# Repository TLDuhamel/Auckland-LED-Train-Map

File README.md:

# Auckland Live LED Train Map

**You can now support my work by buying this through my store:** [**https://keastudios.co.nz/store/akl-ltm/**](https://keastudios.co.nz/store/akl-ltm/)

A physical, real-time LED map of the Auckland train network, powered by an ESP32-C3 microcontroller. Train movements are displayed using addressable RGB LEDs, with live data fetched over Wi-Fi.

---

## Table of Contents

- [Auckland Live LED Train Map](#auckland-live-led-train-map)
  - [Table of Contents](#table-of-contents)
  - [Features](#features)
  - [Hardware](#hardware)
  - [PCB Design](#pcb-design)
  - [Software / Firmware](#software--firmware)
  - [Getting Started](#getting-started)
  - [Web Installer](#web-installer)
  - [Links](#links)
  - [Contributing](#contributing)
  - [License](#license)

---

## Features

- **Real-time Train Tracking:** Displays the approximate locations of trains on the Auckland network.
- **Addressable LEDs:** ~150 WS2812B-compatible RGB LEDs (1.6x1.5mm) for a vibrant display.
- **Wi-Fi Connectivity:** ESP32-C3's built-in Wi-Fi fetches live train data.
- **Custom PCB:** Designed for JLCPCB manufacturing limits.
- **Open Source:** Hardware and firmware are open source.

---

## Hardware

- **Microcontroller:** ESP32-C3 (RISC-V, 160 MHz, 4 MB Flash, QFN32)
- **LEDs:** ~150 x XL-1615RGBC-WS2812B (1.6mm x 1.5mm)
- **PCB:** 249mm x 66mm, JLCPCB-friendly
- **Antenna:** On-board PCB antenna ([TI CC2430DB design](https://www.ti.com/lit/ug/swru125/swru125.pdf))

---

## PCB Design

- Designed in **KiCad V9.0** using [JLCPCB KiCad Library](https://github.com/CDFER/jlcpcb-kicad-library)
- **View Online:** [Interactive PCB Layout (Kicanvas)](https://kicanvas.org/?github=https%3A%2F%2Fgithub.com%2FCDFER%2FAuckland-LED-Train-Map%2Ftree%2Fmain%2FPCB)
- **Source Files:** `/PCB` directory

---

## Software / Firmware

The ESP32-C3 firmware is responsible for:

1. Connecting to Wi-Fi
2. Fetching live train data from the [GTFS Realtime Cache API](https://github.com/CDFER/GTFS-Realtime-Cache-Server)
3. Processing data to determine train locations
4. Controlling WS2812B LEDs to display train positions

---

## Getting Started

1. **Flash the Firmware:**
   - Use the [Web Installer](#web-installer) (recommended, no drivers needed)
   - Or flash manually using PlatformIO (`Firmware/` directory)
2. **Connect to Wi-Fi:**
   - On first boot, use the web interface to configure Wi-Fi credentials.
3. **Power the Board:**
   - Use a 5V USB-C power supply capable of at least 1A.
4. **Enjoy the Live Map!**

---

## Web Installer

Easily flash the latest firmware to your ESP32-C3 using your browser:

[Open the Auckland LED Train Map Web Installer](https://cdfer.github.io/Auckland-LED-Train-Map/led-rails.html)

- Works with Chrome, Edge, or any Web Serial-compatible browser
- Follow on-screen instructions to connect and flash your device

---

## Links

- [Web Installer](https://cdfer.github.io/Auckland-LED-Train-Map/led-rails.html)
- [Interactive PCB Viewer](https://kicanvas.org/?github=https%3A%2F%2Fgithub.com%2FCDFER%2FAuckland-LED-Train-Map%2Ftree%2Fmain%2FPCB)
- [GTFS Realtime Cache API](https://github.com/CDFER/GTFS-Realtime-Cache-Server)
- [JLCPCB KiCad Library](https://github.com/CDFER/jlcpcb-kicad-library)

---

## Contributing

Contributions are welcome! Open an issue or submit a pull request for improvements, bug fixes, or feature suggestions.

---

## License

This project is released under the GPL-3.0-or-later license.

© 2025 Chris Dirks

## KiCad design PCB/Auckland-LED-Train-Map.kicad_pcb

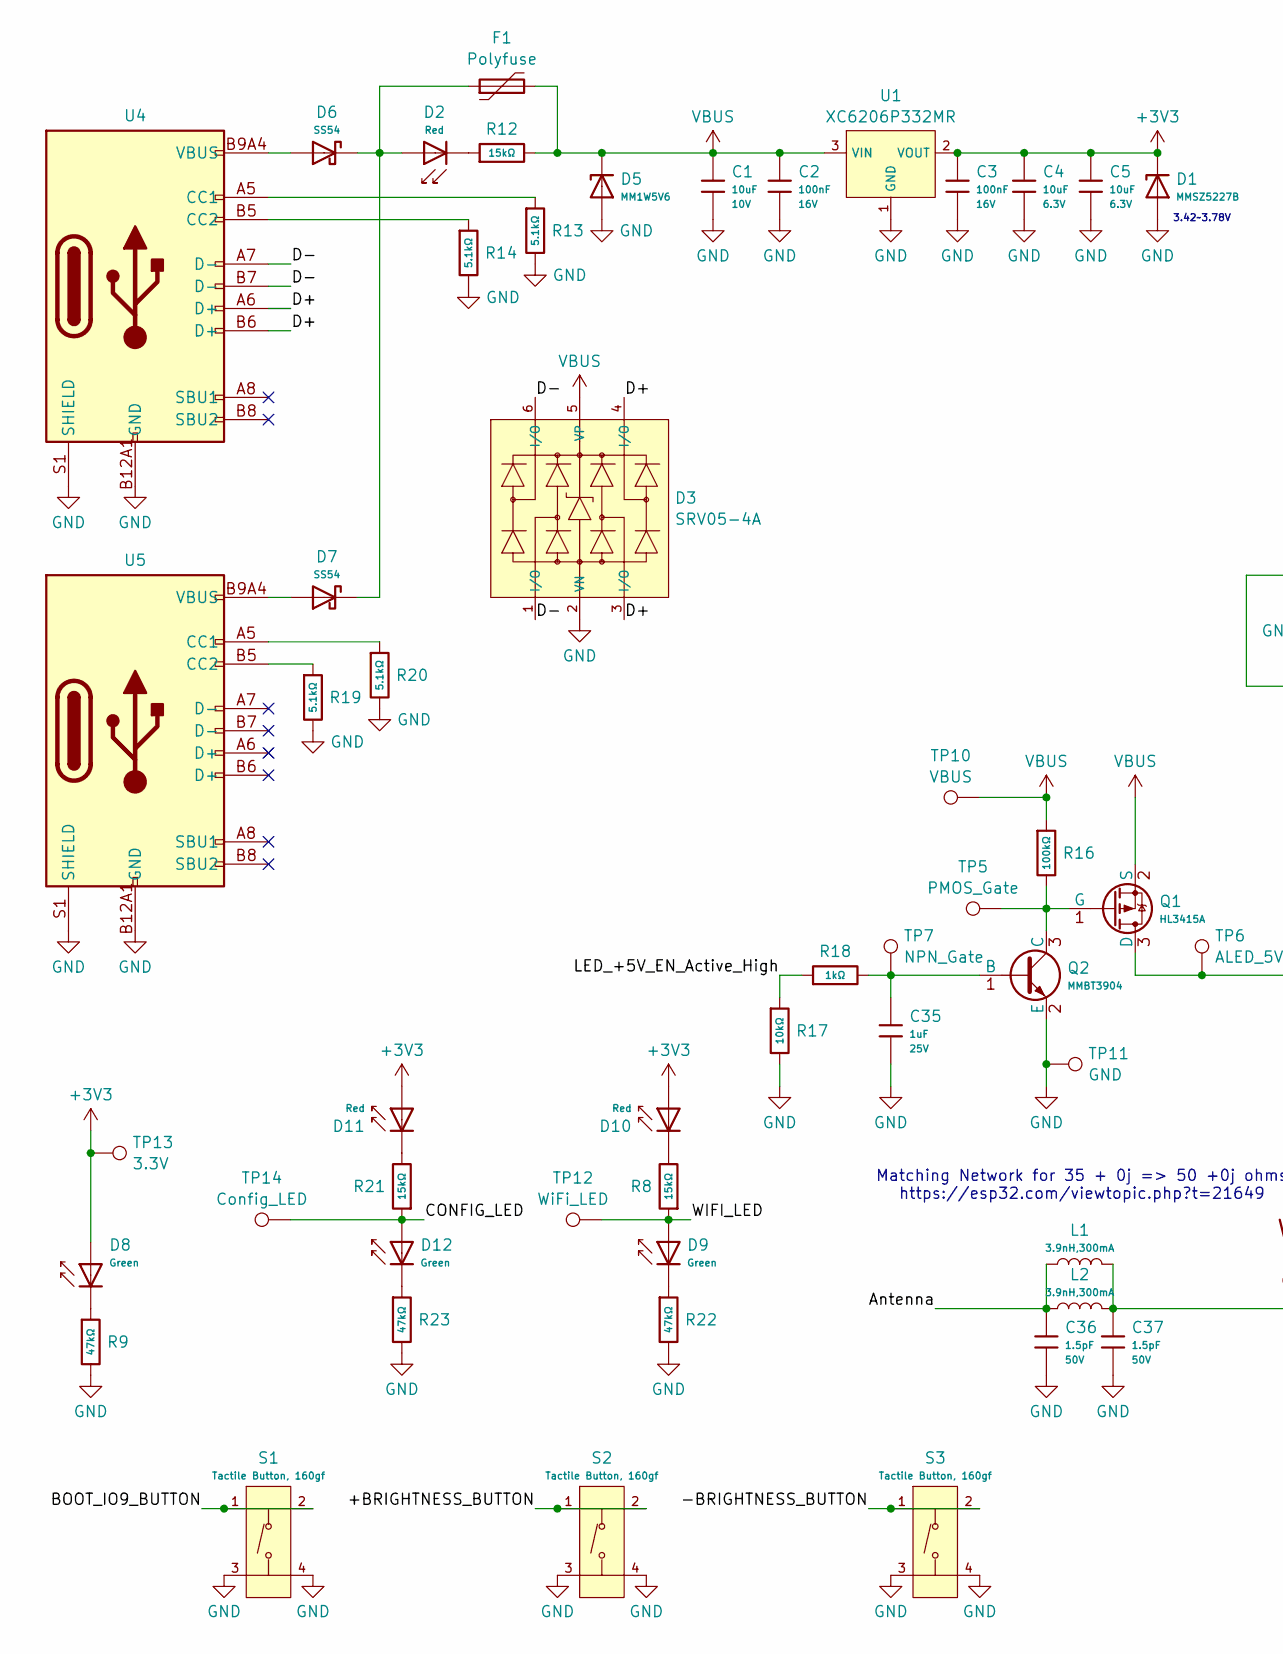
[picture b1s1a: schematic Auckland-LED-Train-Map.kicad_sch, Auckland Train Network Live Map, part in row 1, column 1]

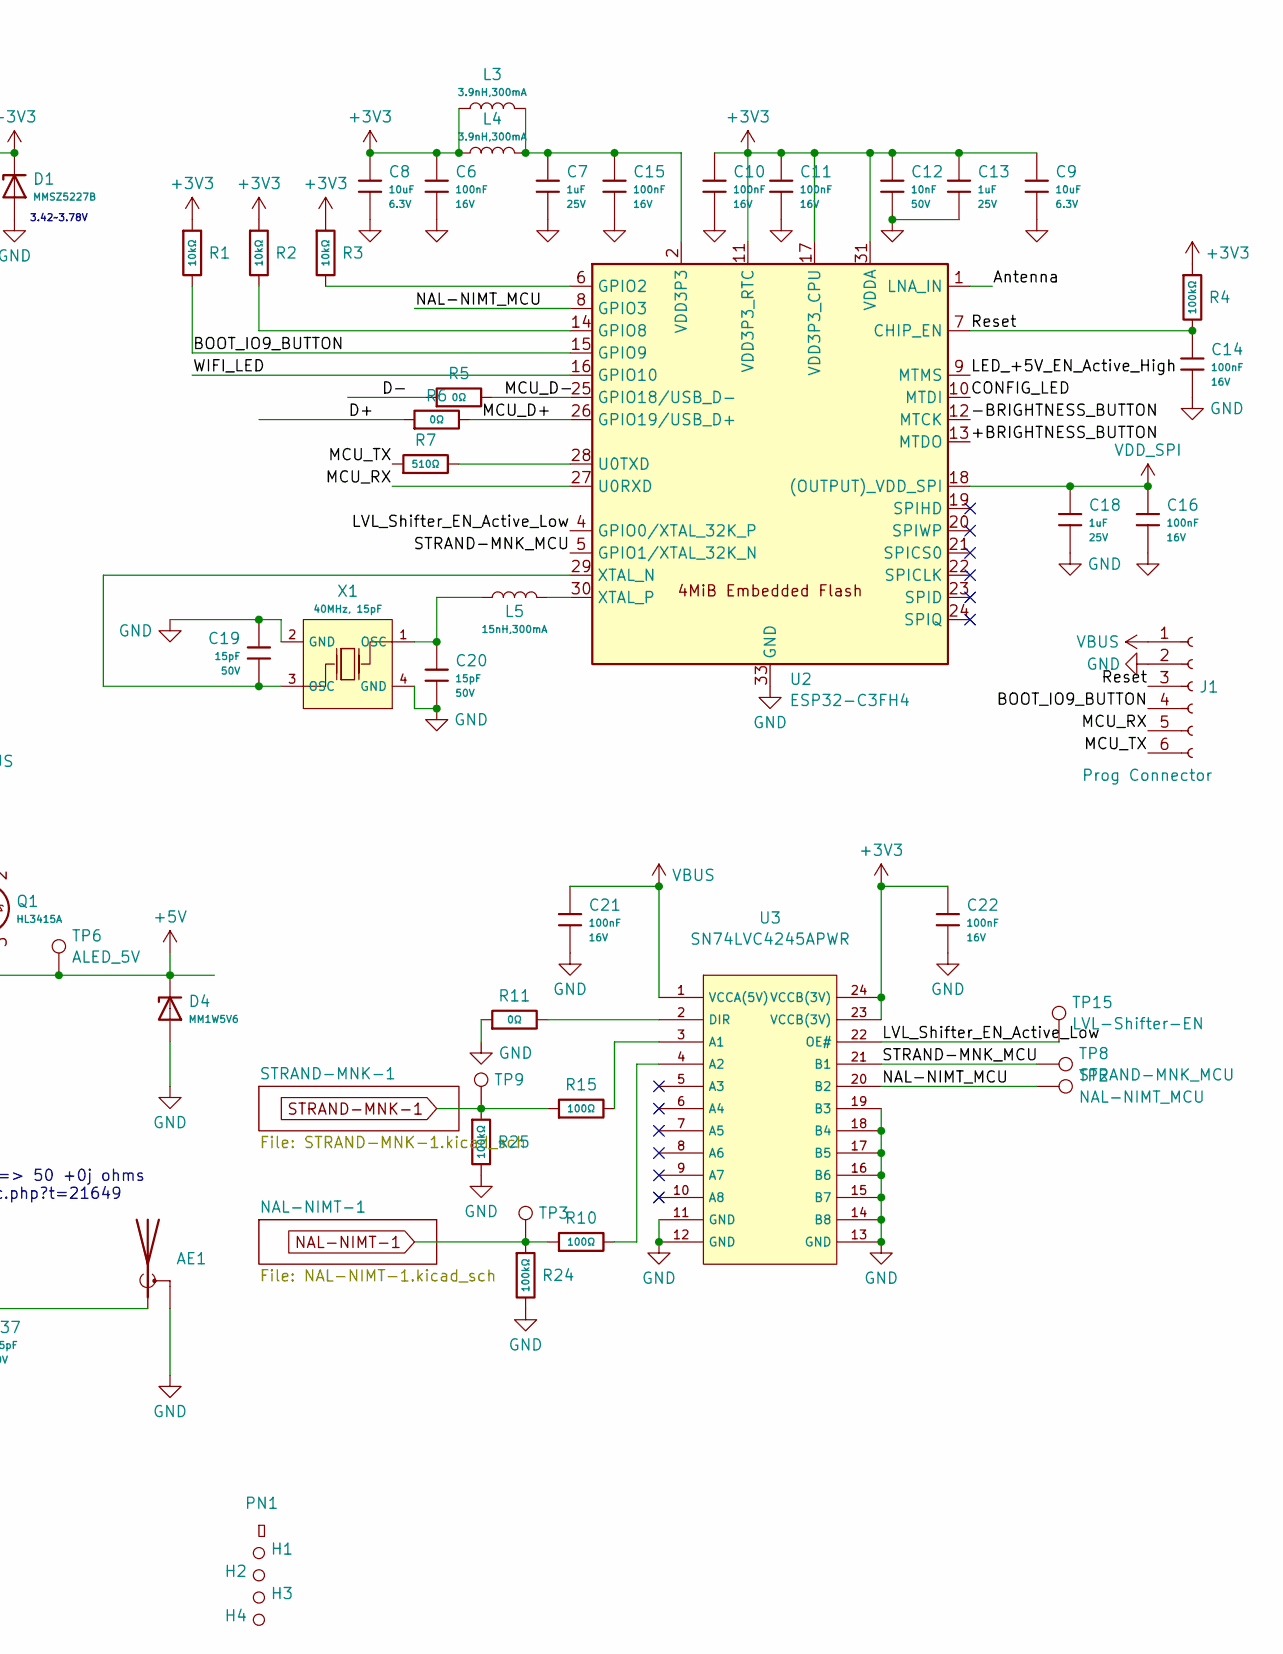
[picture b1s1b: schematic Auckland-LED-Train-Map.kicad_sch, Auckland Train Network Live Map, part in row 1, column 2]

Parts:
AE1: Antenna_Shield; Inverted_F_Antenna_2.4Ghz_1.0mmPCB_TI_CC2430DB.pretty
C1: 10uF; C_0603; Voltage Rated 10V; Tolerance ±10%; Part CL10A106KP8NNNC; LCSC C19702
C2, C3, C6, C10, C11, C14, C15, C16, C21, C22: 100nF; C_0402; Voltage Rated 16V; Tolerance ±10%; Part CL05B104KO5NNNC; LCSC C1525
C4, C5, C8, C9: 10uF; C_0402; Voltage Rated 6.3V; Tolerance ±20%; Part CL05A106MQ5NUNC; LCSC C15525
C7, C13, C18, C35: 1uF; C_0402; Voltage Rated 25V; Tolerance ±10%; Part CL05A105KA5NQNC; LCSC C52923
C12: 10nF; C_0402; Voltage Rated 50V; Tolerance ±10%; Part CL05B103KB5NNNC; LCSC C15195
C19, C20: 15pF; C_0402; Voltage Rated 50V; Tolerance ±5%; Part 0402CG150J500NT; LCSC C1548
C36, C37: 1.5pF; C_0402; Voltage Rated 50V; Part 0402CG1R5C500NT; LCSC C1552
D1: MMSZ5227B; D_SOD-123; Part MMSZ5227B; LCSC C22395553
D2, D10, D11: Red; D_0805; Forward Voltage (VF) 1.6V~2.6V; Part NCD0805R1; LCSC C84256
D3: SRV05-4A; SOT-23-6_L2.9-W1.6-P0.95-LS2.9-BL; Part SRV05-4A; LCSC C20615829
D4, D5: MM1W5V6; D_SOD-123; Part MM1W5V6; LCSC C22435086
D6, D7: SS54; D_SMA; Forward Voltage (Vf@If) 550mV@5A; Reverse Voltage (Vr) 40V; Part SS54; LCSC C22452
D8, D9, D12: Green; D_0805; Part KT-0805G; LCSC C2297
F1: Polyfuse; Fuse_0805_2012Metric_Pad1.15x1.40mm_HandSolder
H1, H2, H3, H4: Hole_Tooling_JLCPCB
J1: Prog Connector
L1, L2, L3, L4: 3.9nH,300mA; L_0402; Part SDCL1005C3N9STDF; LCSC C14033
L5: 15nH,300mA; L_0402; Tolerance ±5%; Part SDCL1005C15NJTDF; LCSC C27143
PN1: Part_Num_JLCPCB
Q1: HL3415A; Q_SOT-23; Part HL3415A; LCSC C28646270
Q2: MMBT3904; Q_SOT-23; Part MMBT3904; LCSC C7420353
R1, R2, R3, R17: 10kΩ; R_0402; Overload Voltage (Max) 50V; Tolerance ±1%; Part 0402WGF1002TCE; LCSC C25744
R4, R16, R24, R25: 100kΩ; R_0402; Overload Voltage (Max) 50V; Tolerance ±1%; Part 0402WGF1003TCE; LCSC C25741
R5, R6, R11: 0Ω; R_0402; Overload Voltage (Max) 50V; Tolerance ±1%; Part 0402WGF0000TCE; LCSC C17168
R7: 510Ω; R_0402; Overload Voltage (Max) 50V; Tolerance ±1%; Part 0402WGF5100TCE; LCSC C25123
R8, R12, R21: 15kΩ; R_0402; Overload Voltage (Max) 50V; Tolerance ±1%; Part 0402WGF1502TCE; LCSC C25756
R9, R22, R23: 47kΩ; R_0402; Overload Voltage (Max) 50V; Tolerance ±1%; Part 0402WGF4702TCE; LCSC C25792
R10, R15: 100Ω; R_0402; Overload Voltage (Max) 50V; Tolerance ±1%; Part 0402WGF1000TCE; LCSC C25076
R13, R14, R19, R20: 5.1kΩ; R_0402; Overload Voltage (Max) 50V; Tolerance ±1%; Part 0402WGF5101TCE; LCSC C25905
R18: 1kΩ; R_0402; Overload Voltage (Max) 50V; Tolerance ±1%; Part 0402WGF1001TCE; LCSC C11702
S1, S2, S3: Tactile Button, 160gf; SW-SMD_4P-L5.1-W5.1-P3.70-LS6.5-TL-2; Voltage Rating (Dc) 12V; Part TS-1187A-B-A-B; LCSC C318884
TP2: NAL-NIMT_MCU; TestPoint_Pad_D1.0mm
TP3: NAL-NIMT_LED; TestPoint_Pad_D1.0mm
TP5: PMOS_Gate; TestPoint_Pad_D1.0mm
TP6: ALED_5V; TestPoint_Pad_D1.0mm
TP7: NPN_Gate; TestPoint_Pad_D1.0mm
TP8: STRAND-MNK_MCU; TestPoint_Pad_D1.0mm
TP9: STRAND-MNK_LED; TestPoint_Pad_D1.0mm
TP10: VBUS; TestPoint_Pad_D1.0mm
TP11: GND; TestPoint_Pad_D1.0mm
TP12: WiFi_LED; TestPoint_Pad_D1.0mm
TP13: 3.3V; TestPoint_Pad_D1.0mm
TP14: Config_LED; TestPoint_Pad_D1.0mm
TP15: LVL-Shifter-EN; TestPoint_Pad_D1.0mm
U1: XC6206P332MR; SOT-23-3_L2.9-W1.6-P1.90-LS2.8-BR; Output Voltage 3.3V; Dropout Voltage 680mV@(100mA); Part XC6206P332MR-G; LCSC C5446
U2: ESP32-C3FH4; QFN-32-1EP_5x5mm_P0.5mm_EP3.7x3.7mm_ThermalVias; LCSC C2858491
U3: SN74LVC4245APWR; TSSOP-24_L7.8-W4.4-P0.65-LS6.4-BL; Part SN74LVC4245APWR; LCSC C7859
U4, U5: Connector, USB-TYPE-C-16P; TYPE-C-SMD_HX-TYPE-C-16PIN; LCSC C2927039
X1: 40MHz, 15pF; OSC-SMD_4P-L3.2-W2.5-BL_SIT8008BI; PartID X322540MPB4SI; LCSC C9010

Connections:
+3V3: C3.1, C4.1, C5.1, C6.1, C8.1, C9.1, C10.1, C11.1, C12.1, C13.1, C22.1, D1.1, D8.2, D10.2, D11.2, L3.1, L4.1, R1.1, R2.1, R3.1, R4.1, TP13.1, U1.2 (VOUT), U2.11 (VDD3P3_RTC), U2.17 (VDD3P3_CPU), U2.31 (VDDA), U2.32 (VDDA), U3.23 (VCCB(3V)), U3.24 (VCCB(3V))
+5V: D4.1, Q1.3 (D), TP6.1; also elsewhere on the board
/+BRIGHTNESS_BUTTON: S2.1 (A), S2.2 (B), U2.13 (MTDO)
/-BRIGHTNESS_BUTTON: S3.1 (A), S3.2 (B), U2.12 (MTCK)
/Antenna: C36.1, L1.1, L2.1, U2.1 (LNA_IN)
/BOOT_IO9_BUTTON: J1.4, R1.2, S1.1 (A), S1.2 (B), U2.15 (GPIO9)
/CONFIG_LED: D12.2, R21.1, TP14.1, U2.10 (MTDI)
/D+: D3.3 (I/O), D3.4 (I/O), R6.1, U4.A6 (D+), U4.B6 (D+)
/D-: D3.1 (I/O), D3.6 (I/O), R5.1, U4.A7 (D-), U4.B7 (D-)
/LED_+5V_EN_Active_High: R17.1, R18.1, U2.9 (MTMS)
/LVL_Shifter_EN_Active_Low: TP15.1, U2.4 (GPIO0/XTAL_32K_P), U3.22 (OE#)
/MCU_D+: R6.2, U2.26 (GPIO19/USB_D+)
/MCU_D-: R5.2, U2.25 (GPIO18/USB_D-)
/MCU_RX: J1.5, U2.27 (U0RXD)
/MCU_TX: J1.6, R7.1
/NAL-NIMT_MCU: TP2.1, U2.8 (GPIO3), U3.20 (B2)
/Reset: C14.1, J1.3, R4.2, U2.7 (CHIP_EN)
/STRAND-MNK_MCU: TP8.1, U2.5 (GPIO1/XTAL_32K_N), U3.21 (B1)
/WIFI_LED: D9.2, R8.1, TP12.1, U2.16 (GPIO10)
GND: AE1.2 (Shield), C1.2, C2.2, C3.2, C4.2, C5.2, C6.2, C7.2, C8.2, C9.2, C10.2, C11.2, C12.2, C13.2, C14.2, C15.2, C16.2, C18.2, C19.2, C20.2, C21.2, C22.2, C35.2, C36.2, C37.2, D1.2, D3.2 (VN), D4.2, D5.2, J1.2, Q2.2 (E), R9.2, R11.1, R13.2, R14.2, R17.2, R19.2, R20.2, R22.2, R23.2, R24.2, R25.2, S1.3 (C), S1.4 (D), S2.3 (C), S2.4 (D), S3.3 (C), S3.4 (D), TP11.1, U1.1 (GND), U2.33 (GND), U3.11 (GND), U3.12 (GND), U3.13 (GND), U3.14 (B8), U3.15 (B7), U3.16 (B6), U3.17 (B5), U3.18 (B4), U3.19 (B3), U4.A12B1 (GND), U4.B12A1 (GND), U4.S1 (SHIELD), U5.A12B1 (GND), U5.B12A1 (GND), U5.S1 (SHIELD), X1.2 (GND), X1.4 (GND); also elsewhere on the board
NAL-NIMT-1: R10.1, R24.1, TP3.1; also elsewhere on the board
unnamed: AE1.1 (A), C37.1, L1.2, L2.2
unnamed: C7.1, C15.1, L3.2, L4.2, U2.2 (VDD3P3), U2.3 (VDD3P3)
unnamed: C20.1, L5.1, X1.1 (OSC)
unnamed: D2.1, R12.1
unnamed: D2.2, D6.1, D7.1, F1.1
unnamed: D6.2, U4.A9B4 (VBUS), U4.B9A4 (VBUS)
unnamed: D7.2, U5.A9B4 (VBUS), U5.B9A4 (VBUS)
unnamed: D8.1, R9.1
unnamed: D9.1, R22.1
unnamed: D10.1, R8.2
unnamed: D11.1, R21.2
unnamed: D12.1, R23.1
unnamed: Q1.1 (G), Q2.3 (C), R16.2, TP5.1
unnamed: C35.1, Q2.1 (B), R18.2, TP7.1
unnamed: R3.2, U2.6 (GPIO2)
unnamed: R2.2, U2.14 (GPIO8)
unnamed: R7.2, U2.28 (U0TXD)
unnamed: C19.1, U2.29 (XTAL_N), X1.3 (OSC)
unnamed: L5.2, U2.30 (XTAL_P)
unnamed: R15.2, U3.3 (A1)
unnamed: R10.2, U3.4 (A2)
unnamed: R11.2, U3.2 (DIR)
unnamed: R13.1, U4.A5 (CC1)
unnamed: R14.1, U4.B5 (CC2)
unnamed: R20.1, U5.A5 (CC1)
unnamed: R19.1, U5.B5 (CC2)
STRAND-MNK-1: R15.1, R25.1, TP9.1; also elsewhere on the board
VBUS: C1.1, C2.1, C21.1, D3.5 (VP), D5.1, F1.2, J1.1, Q1.2 (S), R12.2, R16.1, TP10.1, U1.3 (VIN), U3.1 (VCCA(5V))
VDD_SPI: C16.1, C18.1, U2.18 ((OUTPUT)_VDD_SPI)

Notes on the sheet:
Matching Network for 35 + 0j => 50 +0j ohms https://esp32.com/viewtopic.php?t=21649
3.42~3.78V

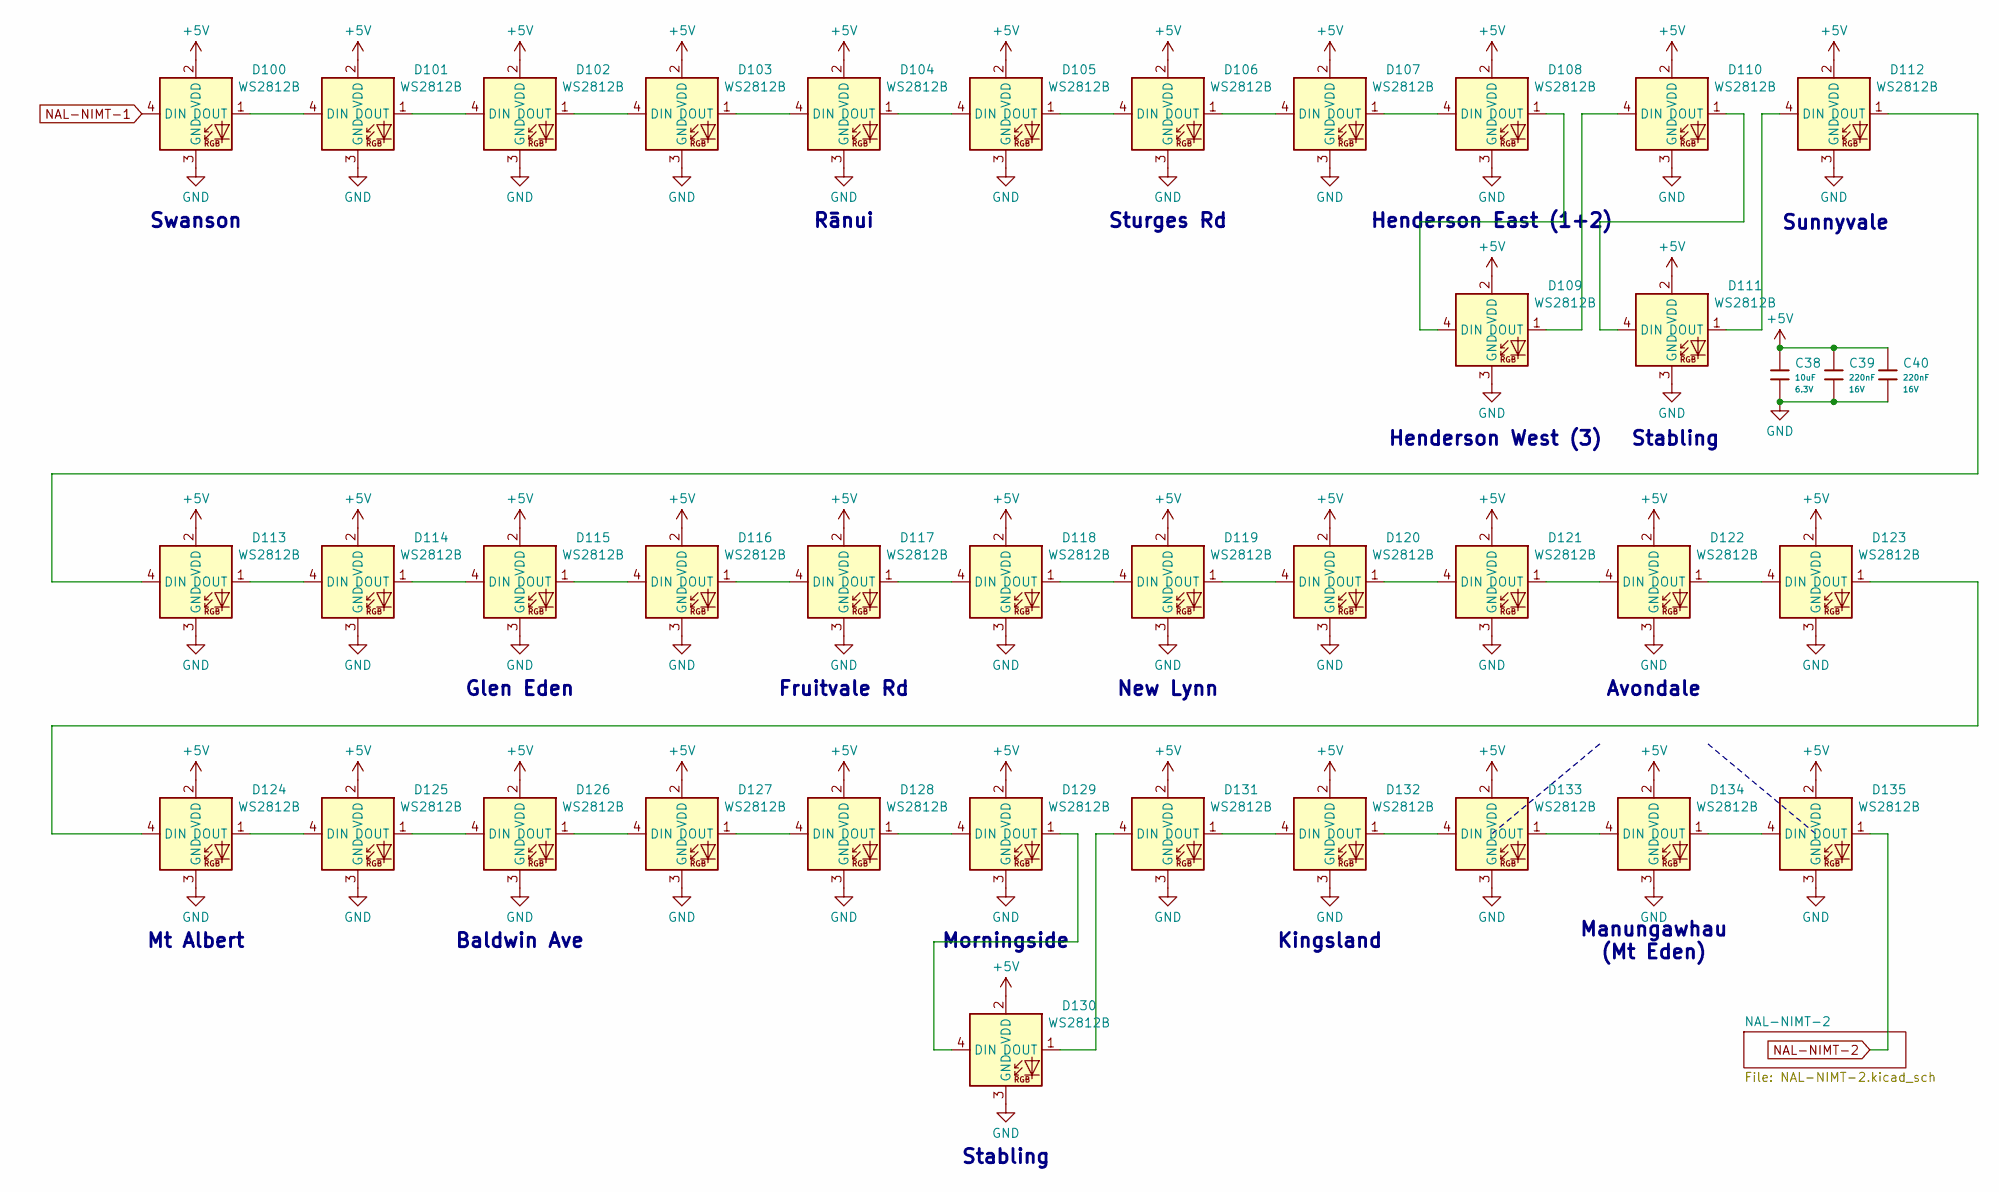
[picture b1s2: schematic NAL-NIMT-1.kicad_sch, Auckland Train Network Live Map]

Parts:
C38: 10uF; C_0402; Voltage Rated 6.3V; Tolerance ±20%; Part CL05A106MQ5NUNC; LCSC C15525
C39, C40: 220nF; C_0402; Voltage Rated 16V; Tolerance ±10%; Part CL05B224KO5NNNC; LCSC C16772
D100, D101, D102, D103, D104, D105, D106, D107, D108, D109, D110, D111, D112, D113, D114, D115, D116, D117, D118, D119, D120, D121, D122, D123, D124, D125, D126, D127, D128, D129, D130, D131, D132, D133, D134, D135: WS2812B; LED-SMD_4P-L1.6-W1.5_XL-1615RGBC-WS2812B; LCSC C5349954

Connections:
+5V: C38.1, C39.1, C40.1, D100.2 (VDD), D101.2 (VDD), D102.2 (VDD), D103.2 (VDD), D104.2 (VDD), D105.2 (VDD), D106.2 (VDD), D107.2 (VDD), D108.2 (VDD), D109.2 (VDD), D110.2 (VDD), D111.2 (VDD), D112.2 (VDD), D113.2 (VDD), D114.2 (VDD), D115.2 (VDD), D116.2 (VDD), D117.2 (VDD), D118.2 (VDD), D119.2 (VDD), D120.2 (VDD), D121.2 (VDD), D122.2 (VDD), D123.2 (VDD), D124.2 (VDD), D125.2 (VDD), D126.2 (VDD), D127.2 (VDD), D128.2 (VDD), D129.2 (VDD), D130.2 (VDD), D131.2 (VDD), D132.2 (VDD), D133.2 (VDD), D134.2 (VDD), D135.2 (VDD); also elsewhere on the board
GND: C38.2, C39.2, C40.2, D100.3 (GND), D101.3 (GND), D102.3 (GND), D103.3 (GND), D104.3 (GND), D105.3 (GND), D106.3 (GND), D107.3 (GND), D108.3 (GND), D109.3 (GND), D110.3 (GND), D111.3 (GND), D112.3 (GND), D113.3 (GND), D114.3 (GND), D115.3 (GND), D116.3 (GND), D117.3 (GND), D118.3 (GND), D119.3 (GND), D120.3 (GND), D121.3 (GND), D122.3 (GND), D123.3 (GND), D124.3 (GND), D125.3 (GND), D126.3 (GND), D127.3 (GND), D128.3 (GND), D129.3 (GND), D130.3 (GND), D131.3 (GND), D132.3 (GND), D133.3 (GND), D134.3 (GND), D135.3 (GND); also elsewhere on the board
NAL-NIMT-1: D100.4 (DIN); also elsewhere on the board
NAL-NIMT-2: D135.1 (DOUT); also elsewhere on the board
unnamed: D100.1 (DOUT), D101.4 (DIN)
unnamed: D101.1 (DOUT), D102.4 (DIN)
unnamed: D102.1 (DOUT), D103.4 (DIN)
unnamed: D103.1 (DOUT), D104.4 (DIN)
unnamed: D104.1 (DOUT), D105.4 (DIN)
unnamed: D105.1 (DOUT), D106.4 (DIN)
unnamed: D106.1 (DOUT), D107.4 (DIN)
unnamed: D107.1 (DOUT), D108.4 (DIN)
unnamed: D108.1 (DOUT), D109.4 (DIN)
unnamed: D109.1 (DOUT), D110.4 (DIN)
unnamed: D110.1 (DOUT), D111.4 (DIN)
unnamed: D111.1 (DOUT), D112.4 (DIN)
unnamed: D112.1 (DOUT), D113.4 (DIN)
unnamed: D113.1 (DOUT), D114.4 (DIN)
unnamed: D114.1 (DOUT), D115.4 (DIN)
unnamed: D115.1 (DOUT), D116.4 (DIN)
unnamed: D116.1 (DOUT), D117.4 (DIN)
unnamed: D117.1 (DOUT), D118.4 (DIN)
unnamed: D118.1 (DOUT), D119.4 (DIN)
unnamed: D119.1 (DOUT), D120.4 (DIN)
unnamed: D120.1 (DOUT), D121.4 (DIN)
unnamed: D121.1 (DOUT), D122.4 (DIN)
unnamed: D122.1 (DOUT), D123.4 (DIN)
unnamed: D123.1 (DOUT), D124.4 (DIN)
unnamed: D124.1 (DOUT), D125.4 (DIN)
unnamed: D125.1 (DOUT), D126.4 (DIN)
unnamed: D126.1 (DOUT), D127.4 (DIN)
unnamed: D127.1 (DOUT), D128.4 (DIN)
unnamed: D128.1 (DOUT), D129.4 (DIN)
unnamed: D129.1 (DOUT), D130.4 (DIN)
unnamed: D130.1 (DOUT), D131.4 (DIN)
unnamed: D131.1 (DOUT), D132.4 (DIN)
unnamed: D132.1 (DOUT), D133.4 (DIN)
unnamed: D133.1 (DOUT), D134.4 (DIN)
unnamed: D134.1 (DOUT), D135.4 (DIN)

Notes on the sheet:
Henderson East (1+2)
Rānui
Henderson West (3)
Stabling
Mt Albert
Baldwin Ave
New Lynn
Kingsland
Manungawhau (Mt Eden)
Fruitvale Rd
Sunnyvale
Swanson
Sturges Rd
Glen Eden
Avondale
Morningside

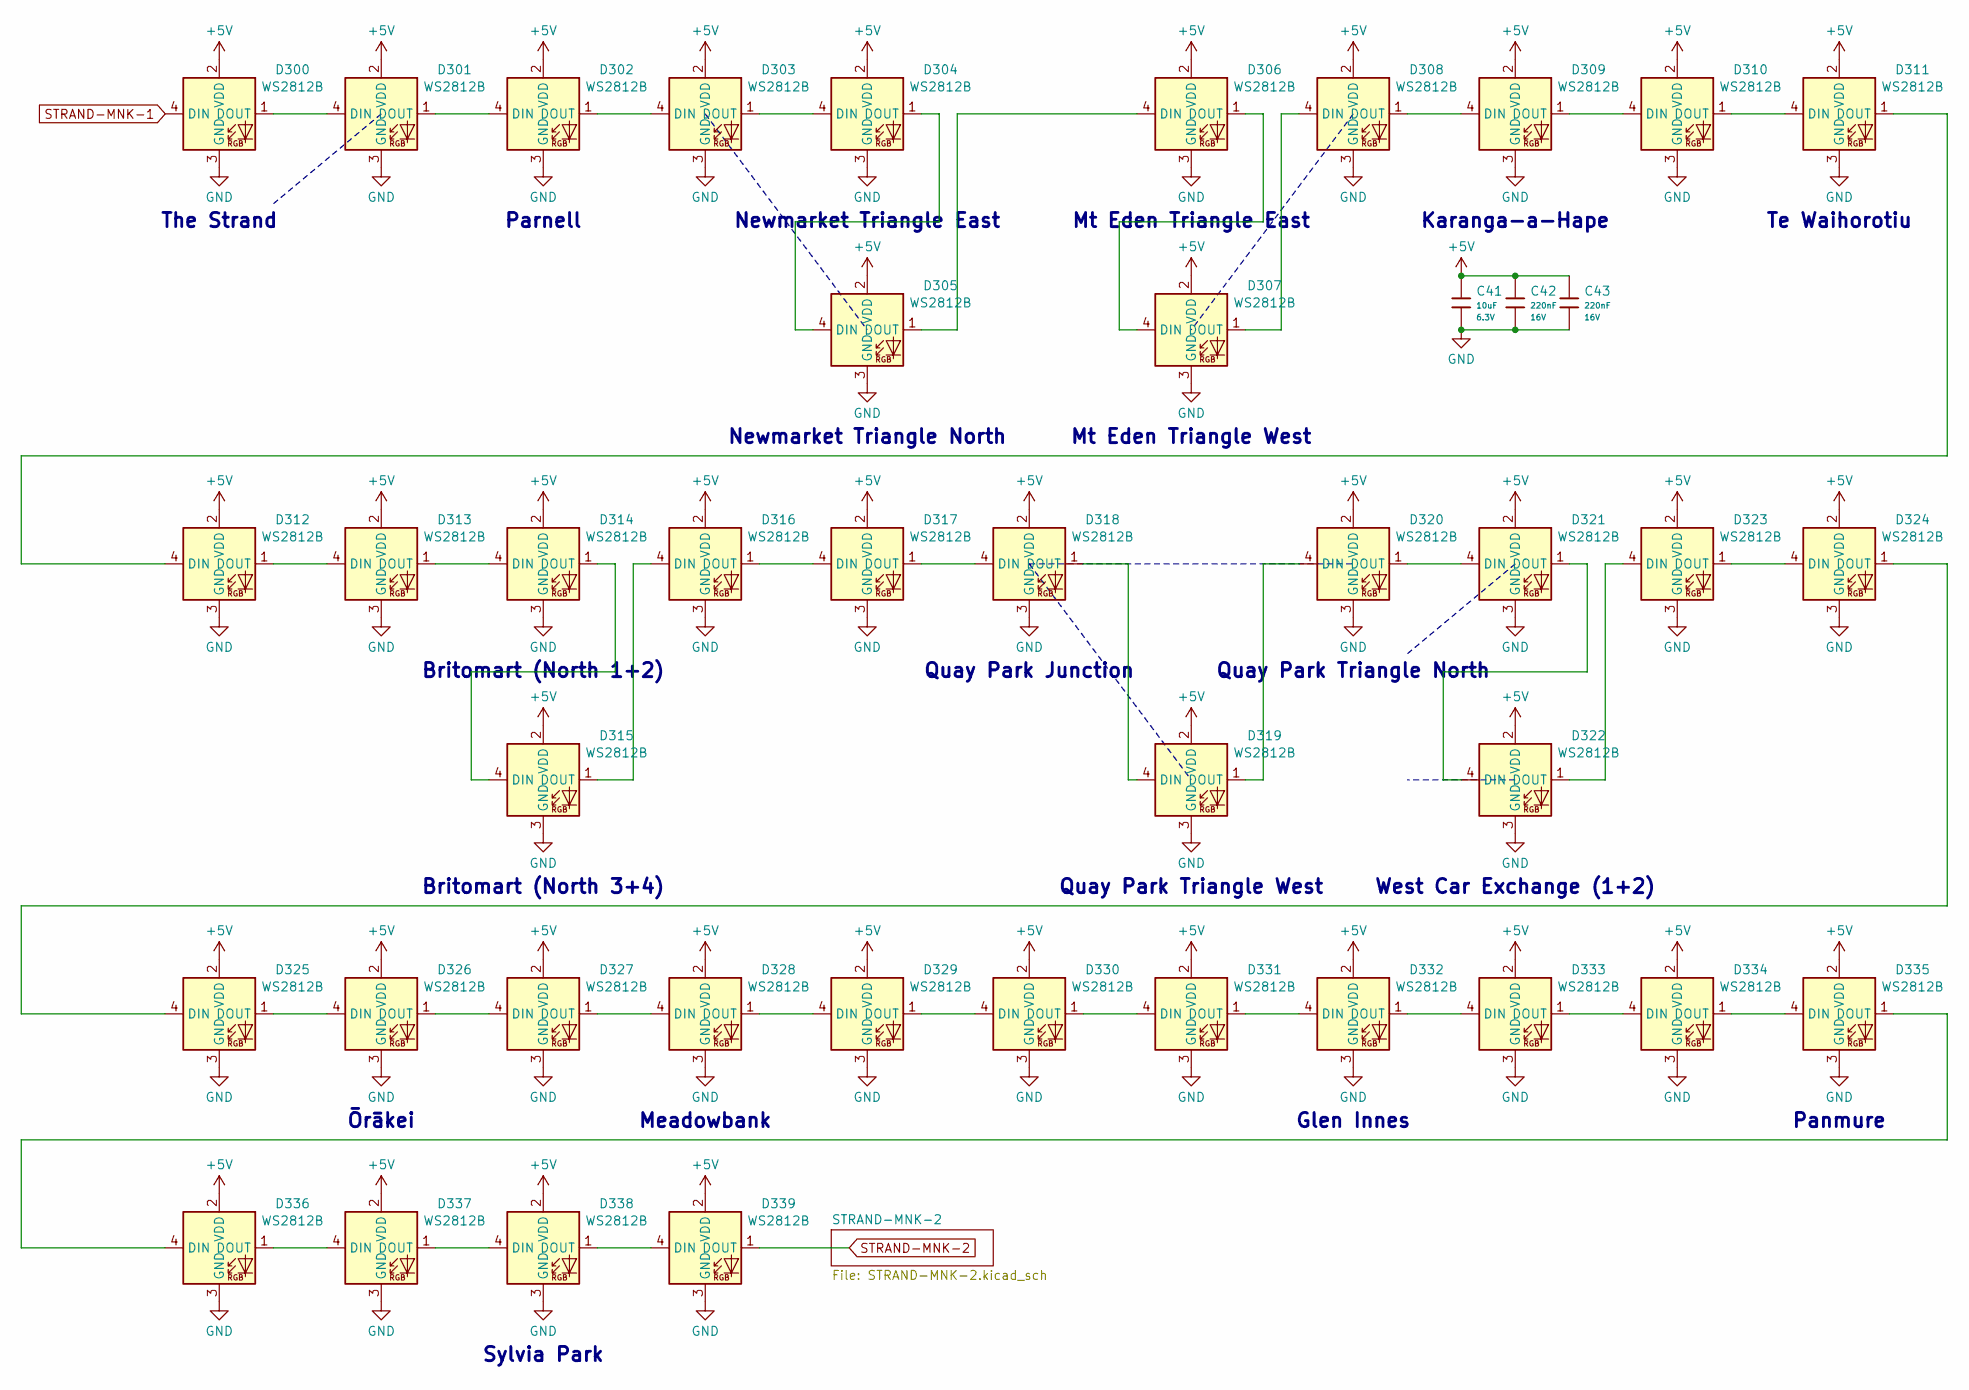
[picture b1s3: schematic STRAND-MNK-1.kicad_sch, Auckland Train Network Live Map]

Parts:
C41: 10uF; C_0402; Voltage Rated 6.3V; Tolerance ±20%; Part CL05A106MQ5NUNC; LCSC C15525
C42, C43: 220nF; C_0402; Voltage Rated 16V; Tolerance ±10%; Part CL05B224KO5NNNC; LCSC C16772
D300, D301, D302, D303, D304, D305, D306, D307, D308, D309, D310, D311, D312, D313, D314, D315, D316, D317, D318, D319, D320, D321, D322, D323, D324, D325, D326, D327, D328, D329, D330, D331, D332, D333, D334, D335, D336, D337, D338, D339: WS2812B; LED-SMD_4P-L1.6-W1.5_XL-1615RGBC-WS2812B; LCSC C5349954

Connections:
+5V: C41.1, C42.1, C43.1, D300.2 (VDD), D301.2 (VDD), D302.2 (VDD), D303.2 (VDD), D304.2 (VDD), D305.2 (VDD), D306.2 (VDD), D307.2 (VDD), D308.2 (VDD), D309.2 (VDD), D310.2 (VDD), D311.2 (VDD), D312.2 (VDD), D313.2 (VDD), D314.2 (VDD), D315.2 (VDD), D316.2 (VDD), D317.2 (VDD), D318.2 (VDD), D319.2 (VDD), D320.2 (VDD), D321.2 (VDD), D322.2 (VDD), D323.2 (VDD), D324.2 (VDD), D325.2 (VDD), D326.2 (VDD), D327.2 (VDD), D328.2 (VDD), D329.2 (VDD), D330.2 (VDD), D331.2 (VDD), D332.2 (VDD), D333.2 (VDD), D334.2 (VDD), D335.2 (VDD), D336.2 (VDD), D337.2 (VDD), D338.2 (VDD), D339.2 (VDD); also elsewhere on the board
GND: C41.2, C42.2, C43.2, D300.3 (GND), D301.3 (GND), D302.3 (GND), D303.3 (GND), D304.3 (GND), D305.3 (GND), D306.3 (GND), D307.3 (GND), D308.3 (GND), D309.3 (GND), D310.3 (GND), D311.3 (GND), D312.3 (GND), D313.3 (GND), D314.3 (GND), D315.3 (GND), D316.3 (GND), D317.3 (GND), D318.3 (GND), D319.3 (GND), D320.3 (GND), D321.3 (GND), D322.3 (GND), D323.3 (GND), D324.3 (GND), D325.3 (GND), D326.3 (GND), D327.3 (GND), D328.3 (GND), D329.3 (GND), D330.3 (GND), D331.3 (GND), D332.3 (GND), D333.3 (GND), D334.3 (GND), D335.3 (GND), D336.3 (GND), D337.3 (GND), D338.3 (GND), D339.3 (GND); also elsewhere on the board
unnamed: D300.1 (DOUT), D301.4 (DIN)
unnamed: D301.1 (DOUT), D302.4 (DIN)
unnamed: D302.1 (DOUT), D303.4 (DIN)
unnamed: D303.1 (DOUT), D304.4 (DIN)
unnamed: D304.1 (DOUT), D305.4 (DIN)
unnamed: D305.1 (DOUT), D306.4 (DIN)
unnamed: D306.1 (DOUT), D307.4 (DIN)
unnamed: D307.1 (DOUT), D308.4 (DIN)
unnamed: D308.1 (DOUT), D309.4 (DIN)
unnamed: D309.1 (DOUT), D310.4 (DIN)
unnamed: D310.1 (DOUT), D311.4 (DIN)
unnamed: D311.1 (DOUT), D312.4 (DIN)
unnamed: D312.1 (DOUT), D313.4 (DIN)
unnamed: D313.1 (DOUT), D314.4 (DIN)
unnamed: D314.1 (DOUT), D315.4 (DIN)
unnamed: D315.1 (DOUT), D316.4 (DIN)
unnamed: D316.1 (DOUT), D317.4 (DIN)
unnamed: D317.1 (DOUT), D318.4 (DIN)
unnamed: D318.1 (DOUT), D319.4 (DIN)
unnamed: D319.1 (DOUT), D320.4 (DIN)
unnamed: D320.1 (DOUT), D321.4 (DIN)
unnamed: D321.1 (DOUT), D322.4 (DIN)
unnamed: D322.1 (DOUT), D323.4 (DIN)
unnamed: D323.1 (DOUT), D324.4 (DIN)
unnamed: D324.1 (DOUT), D325.4 (DIN)
unnamed: D325.1 (DOUT), D326.4 (DIN)
unnamed: D326.1 (DOUT), D327.4 (DIN)
unnamed: D327.1 (DOUT), D328.4 (DIN)
unnamed: D328.1 (DOUT), D329.4 (DIN)
unnamed: D329.1 (DOUT), D330.4 (DIN)
unnamed: D330.1 (DOUT), D331.4 (DIN)
unnamed: D331.1 (DOUT), D332.4 (DIN)
unnamed: D332.1 (DOUT), D333.4 (DIN)
unnamed: D333.1 (DOUT), D334.4 (DIN)
unnamed: D334.1 (DOUT), D335.4 (DIN)
unnamed: D335.1 (DOUT), D336.4 (DIN)
unnamed: D336.1 (DOUT), D337.4 (DIN)
unnamed: D337.1 (DOUT), D338.4 (DIN)
unnamed: D338.1 (DOUT), D339.4 (DIN)
STRAND-MNK-1: D300.4 (DIN); also elsewhere on the board
STRAND-MNK-2: D339.1 (DOUT); also elsewhere on the board

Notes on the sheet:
Britomart (North 1+2)
Quay Park Triangle North
Panmure
Parnell
Te Waihorotiu
Meadowbank
Mt Eden Triangle West
Newmarket Triangle East
Quay Park Junction
Quay Park Triangle West
Ōrākei
Glen Innes
Newmarket Triangle North
Mt Eden Triangle East
The Strand
Sylvia Park
Karanga-a-Hape
West Car Exchange (1+2)
Britomart (North 3+4)

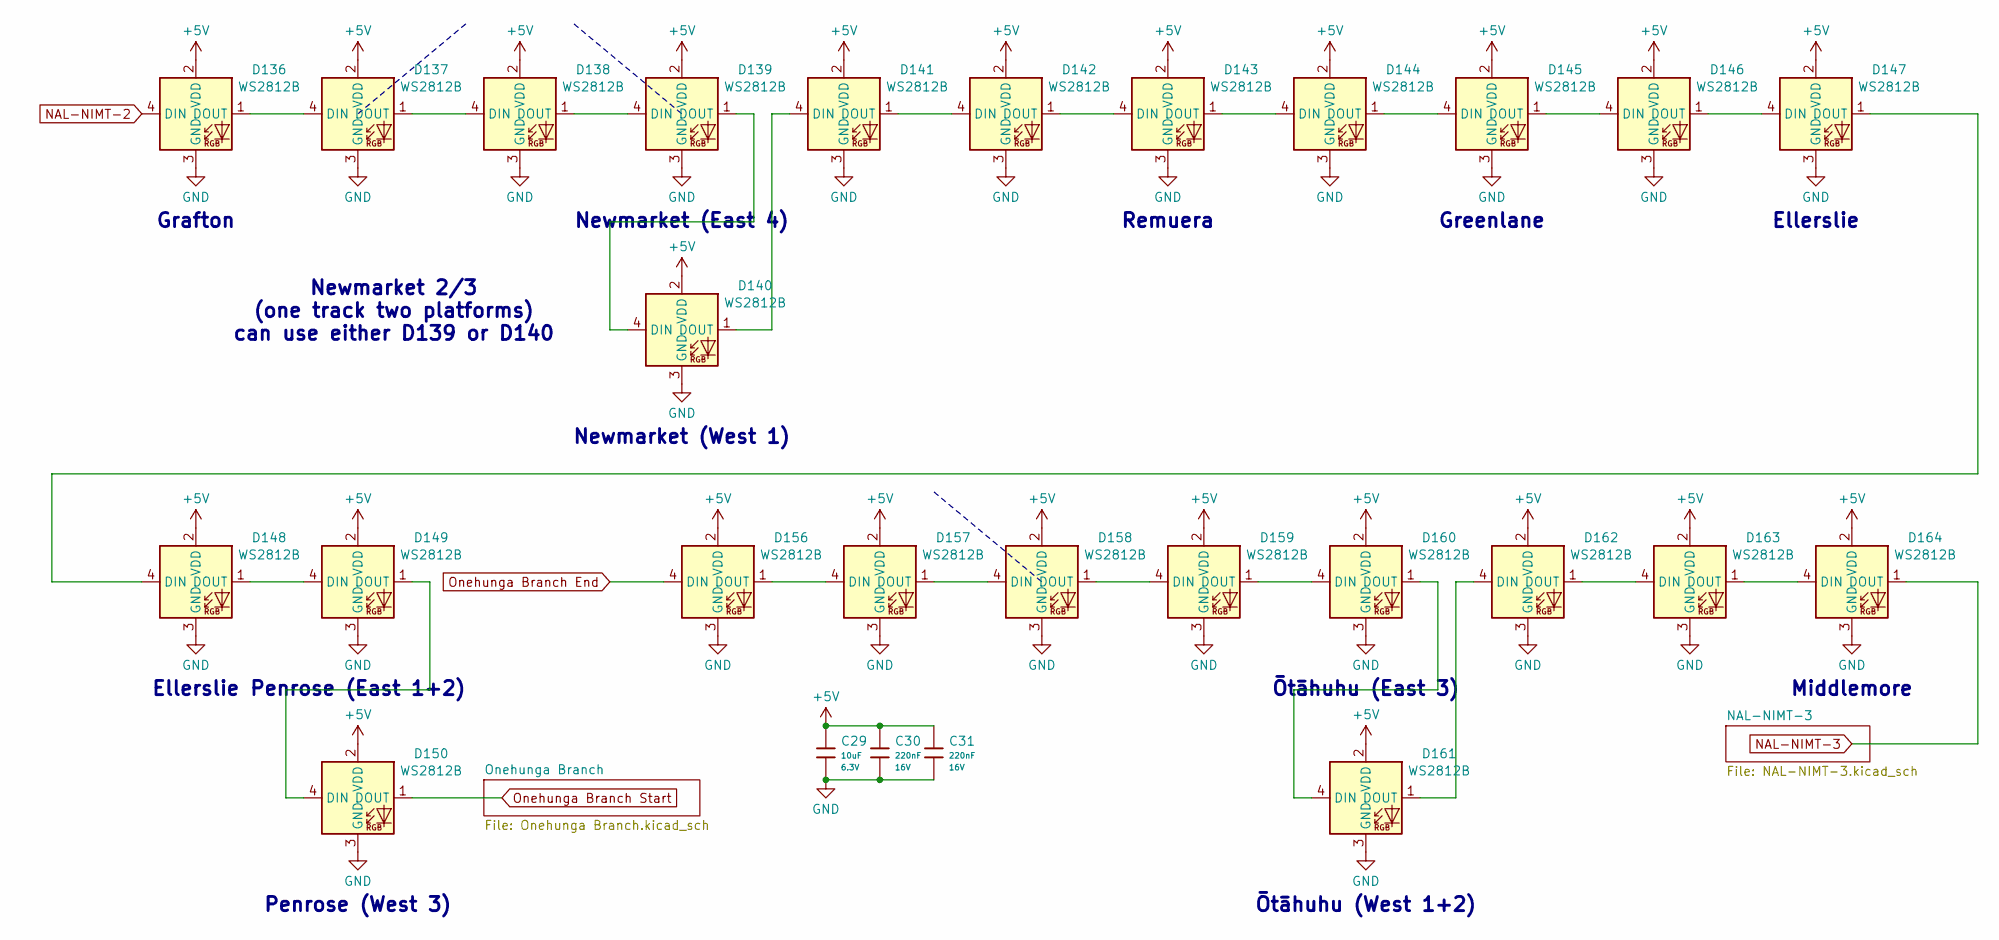
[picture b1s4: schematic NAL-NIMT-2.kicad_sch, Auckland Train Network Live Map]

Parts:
C29: 10uF; C_0402; Voltage Rated 6.3V; Tolerance ±20%; Part CL05A106MQ5NUNC; LCSC C15525
C30, C31: 220nF; C_0402; Voltage Rated 16V; Tolerance ±10%; Part CL05B224KO5NNNC; LCSC C16772
D136, D137, D138, D139, D140, D141, D142, D143, D144, D145, D146, D147, D148, D149, D150, D156, D157, D158, D159, D160, D161, D162, D163, D164: WS2812B; LED-SMD_4P-L1.6-W1.5_XL-1615RGBC-WS2812B; LCSC C5349954

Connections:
+5V: C29.1, C30.1, C31.1, D136.2 (VDD), D137.2 (VDD), D138.2 (VDD), D139.2 (VDD), D140.2 (VDD), D141.2 (VDD), D142.2 (VDD), D143.2 (VDD), D144.2 (VDD), D145.2 (VDD), D146.2 (VDD), D147.2 (VDD), D148.2 (VDD), D149.2 (VDD), D150.2 (VDD), D156.2 (VDD), D157.2 (VDD), D158.2 (VDD), D159.2 (VDD), D160.2 (VDD), D161.2 (VDD), D162.2 (VDD), D163.2 (VDD), D164.2 (VDD); also elsewhere on the board
GND: C29.2, C30.2, C31.2, D136.3 (GND), D137.3 (GND), D138.3 (GND), D139.3 (GND), D140.3 (GND), D141.3 (GND), D142.3 (GND), D143.3 (GND), D144.3 (GND), D145.3 (GND), D146.3 (GND), D147.3 (GND), D148.3 (GND), D149.3 (GND), D150.3 (GND), D156.3 (GND), D157.3 (GND), D158.3 (GND), D159.3 (GND), D160.3 (GND), D161.3 (GND), D162.3 (GND), D163.3 (GND), D164.3 (GND); also elsewhere on the board
NAL-NIMT-2: D136.4 (DIN); also elsewhere on the board
NAL-NIMT-3: D164.1 (DOUT); also elsewhere on the board
unnamed: D136.1 (DOUT), D137.4 (DIN)
unnamed: D137.1 (DOUT), D138.4 (DIN)
unnamed: D138.1 (DOUT), D139.4 (DIN)
unnamed: D139.1 (DOUT), D140.4 (DIN)
unnamed: D140.1 (DOUT), D141.4 (DIN)
unnamed: D141.1 (DOUT), D142.4 (DIN)
unnamed: D142.1 (DOUT), D143.4 (DIN)
unnamed: D143.1 (DOUT), D144.4 (DIN)
unnamed: D144.1 (DOUT), D145.4 (DIN)
unnamed: D145.1 (DOUT), D146.4 (DIN)
unnamed: D146.1 (DOUT), D147.4 (DIN)
unnamed: D147.1 (DOUT), D148.4 (DIN)
unnamed: D148.1 (DOUT), D149.4 (DIN)
unnamed: D149.1 (DOUT), D150.4 (DIN)
unnamed: D156.1 (DOUT), D157.4 (DIN)
unnamed: D157.1 (DOUT), D158.4 (DIN)
unnamed: D158.1 (DOUT), D159.4 (DIN)
unnamed: D159.1 (DOUT), D160.4 (DIN)
unnamed: D160.1 (DOUT), D161.4 (DIN)
unnamed: D161.1 (DOUT), D162.4 (DIN)
unnamed: D162.1 (DOUT), D163.4 (DIN)
unnamed: D163.1 (DOUT), D164.4 (DIN)
Onehunga Branch End: D156.4 (DIN); also elsewhere on the board
Onehunga Branch Start: D150.1 (DOUT); also elsewhere on the board

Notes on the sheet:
Middlemore
Greenlane
Ōtāhuhu (East 3)
Newmarket 2/3 (one track two platforms) can use either D139 or D140
Ellerslie
Grafton
Newmarket (East 4)
Remuera
Ōtāhuhu (West 1+2)
Newmarket (West 1)
Penrose (West 3)
Penrose (East 1+2)

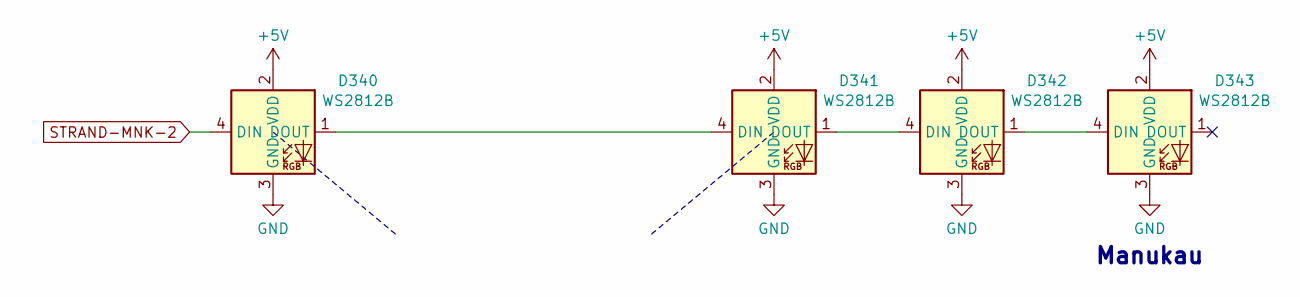
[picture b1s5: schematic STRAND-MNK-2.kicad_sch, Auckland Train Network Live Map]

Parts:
D340, D341, D342, D343: WS2812B; LED-SMD_4P-L1.6-W1.5_XL-1615RGBC-WS2812B; LCSC C5349954

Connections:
+5V: D340.2 (VDD), D341.2 (VDD), D342.2 (VDD), D343.2 (VDD); also elsewhere on the board
GND: D340.3 (GND), D341.3 (GND), D342.3 (GND), D343.3 (GND); also elsewhere on the board
unnamed: D340.1 (DOUT), D341.4 (DIN)
unnamed: D341.1 (DOUT), D342.4 (DIN)
unnamed: D342.1 (DOUT), D343.4 (DIN)
STRAND-MNK-2: D340.4 (DIN); also elsewhere on the board

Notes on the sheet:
Manukau

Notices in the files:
PCB/Auckland-LED-Train-Map.kicad_pcb:
©Chris Dirks
MIT License
README.md:
Hardware, Software and Documentation License: GPL-3.0-or-later
